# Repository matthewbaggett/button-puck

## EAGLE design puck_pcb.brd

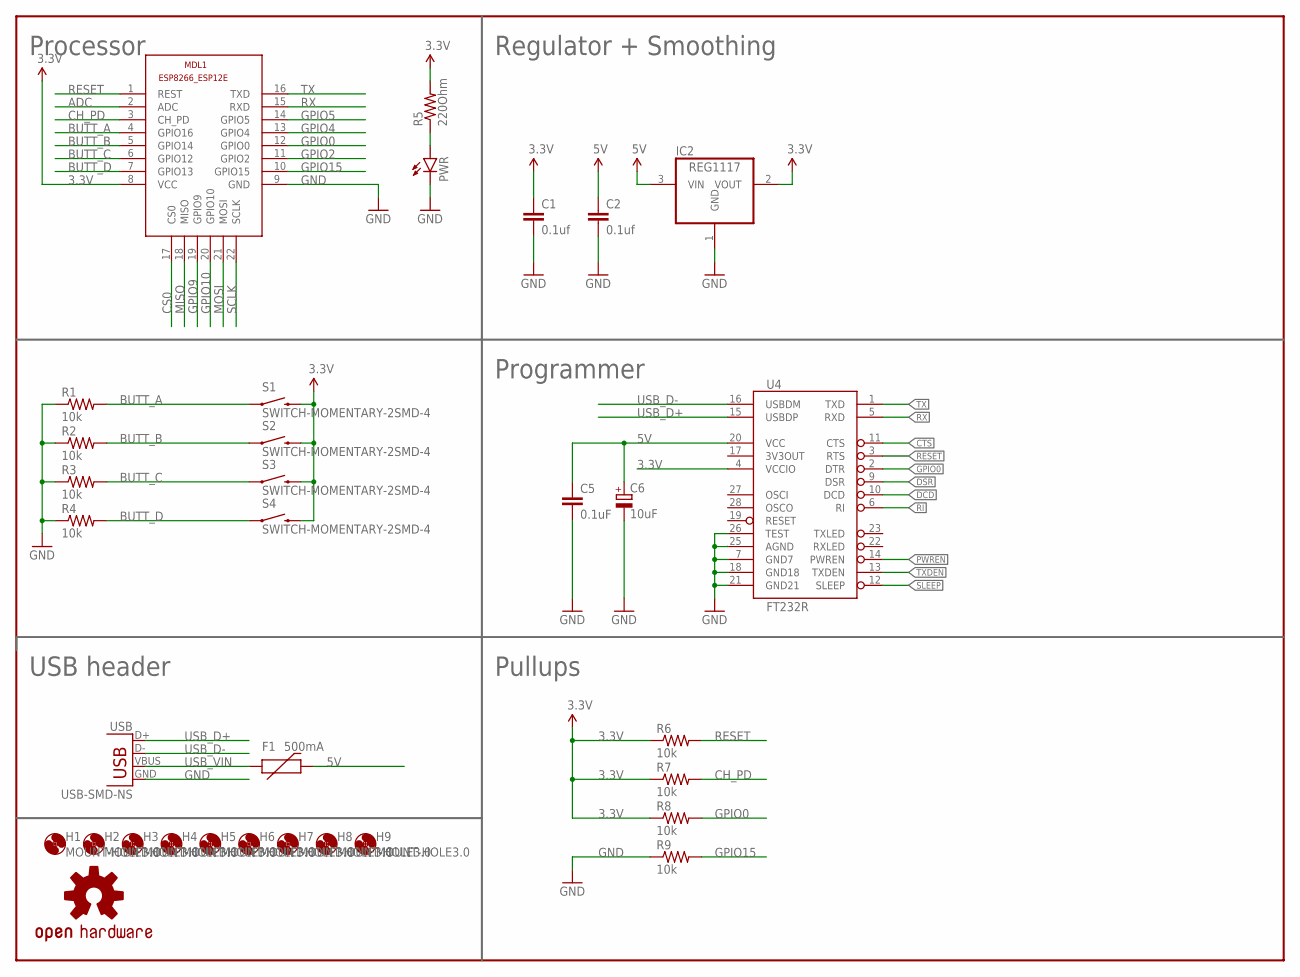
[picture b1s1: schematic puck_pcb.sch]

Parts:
C1, C2: 0.1uf; 1206
C5: 0.1uF; C1206K
C6: 10uF; SMC_A
F1: 500mA; PTC-1206
FRAME2: FRAME-LETTERNO_PACKAGE; DUMMY
H1, H2, H3, H4, H5, H6, H7, H8, H9: MOUNT-HOLE3.0; 3,0
IC2: REG1117; SOT223
LOGO1: OSHW-LOGOS; OSHW-LOGO-S
MDL1: ESP8266-12EESP8266-ESP12E; ESP8266-ESP12E
PWR: LED1206; LED-1206
R1, R2, R3, R4, R6, R7, R8, R9: 10k; 1206
R5: 220Ohm; 1206
S1, S2, S3, S4: SWITCH-MOMENTARY-2SMD-4; TACTILE_SWITCH_TALL
U4: FT232R; SSOP28DB
USB: USB-SMD-NS; USB-MINIB-NOSTOP

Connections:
3.3V: C1.1, IC2.2 (VOUT), MDL1.8 (VCC), R5.2, R6.1, R7.1, R8.1, S1.B2 (2), S2.B2 (2), S3.B2 (2), S4.B2 (2), U4.4 (VCCIO)
5V: C2.1, C5.1, C6.+, F1.2, IC2.3 (VIN), U4.20 (VCC)
ADC: MDL1.2 (ADC)
BUTT_A: MDL1.4 (GPIO16), R1.2, S1.A2 (1)
BUTT_B: MDL1.5 (GPIO14), R2.2, S2.A2 (1)
BUTT_C: MDL1.6 (GPIO12), R3.2, S3.A2 (1)
BUTT_D: MDL1.7 (GPIO13), R4.2, S4.A2 (1)
CH_PD: MDL1.3 (CH_PD), R7.2
CS0: MDL1.17 (CS0)
CTS: U4.11 (CTS)
DCD: U4.10 (DCD)
DSR: U4.9 (DSR)
GND: C1.2, C2.2, C5.2, C6.-, IC2.1 (GND), MDL1.9 (GND), PWR.C, R1.1, R2.1, R3.1, R4.1, R9.1, U4.7 (GND7), U4.18 (GND18), U4.21 (GND21), U4.25 (AGND), U4.26 (TEST), USB.GND
GPIO0: MDL1.12 (GPIO0), R8.2, U4.2 (DTR)
GPIO2: MDL1.11 (GPIO2)
GPIO4: MDL1.13 (GPIO4)
GPIO5: MDL1.14 (GPIO5)
GPIO9: MDL1.19 (GPIO9)
GPIO10: MDL1.20 (GPIO10)
GPIO15: MDL1.10 (GPIO15), R9.2
MISO: MDL1.18 (MISO)
MOSI: MDL1.21 (MOSI)
unnamed: PWR.A, R5.1
PWREN: U4.14 (PWREN)
RESET: MDL1.1 (REST), R6.2, U4.3 (RTS)
RI: U4.6 (RI)
RX: MDL1.15 (RXD), U4.5 (RXD)
SCLK: MDL1.22 (SCLK)
SLEEP: U4.12 (SLEEP)
TX: MDL1.16 (TXD), U4.1 (TXD)
TXDEN: U4.13 (TXDEN)
USB_D+: U4.15 (USBDP), USB.D+
USB_D-: U4.16 (USBDM), USB.D-
USB_VIN: F1.1, USB.VBUS

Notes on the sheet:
Programmer
Regulator + Smoothing
Processor
USB header
Pullups

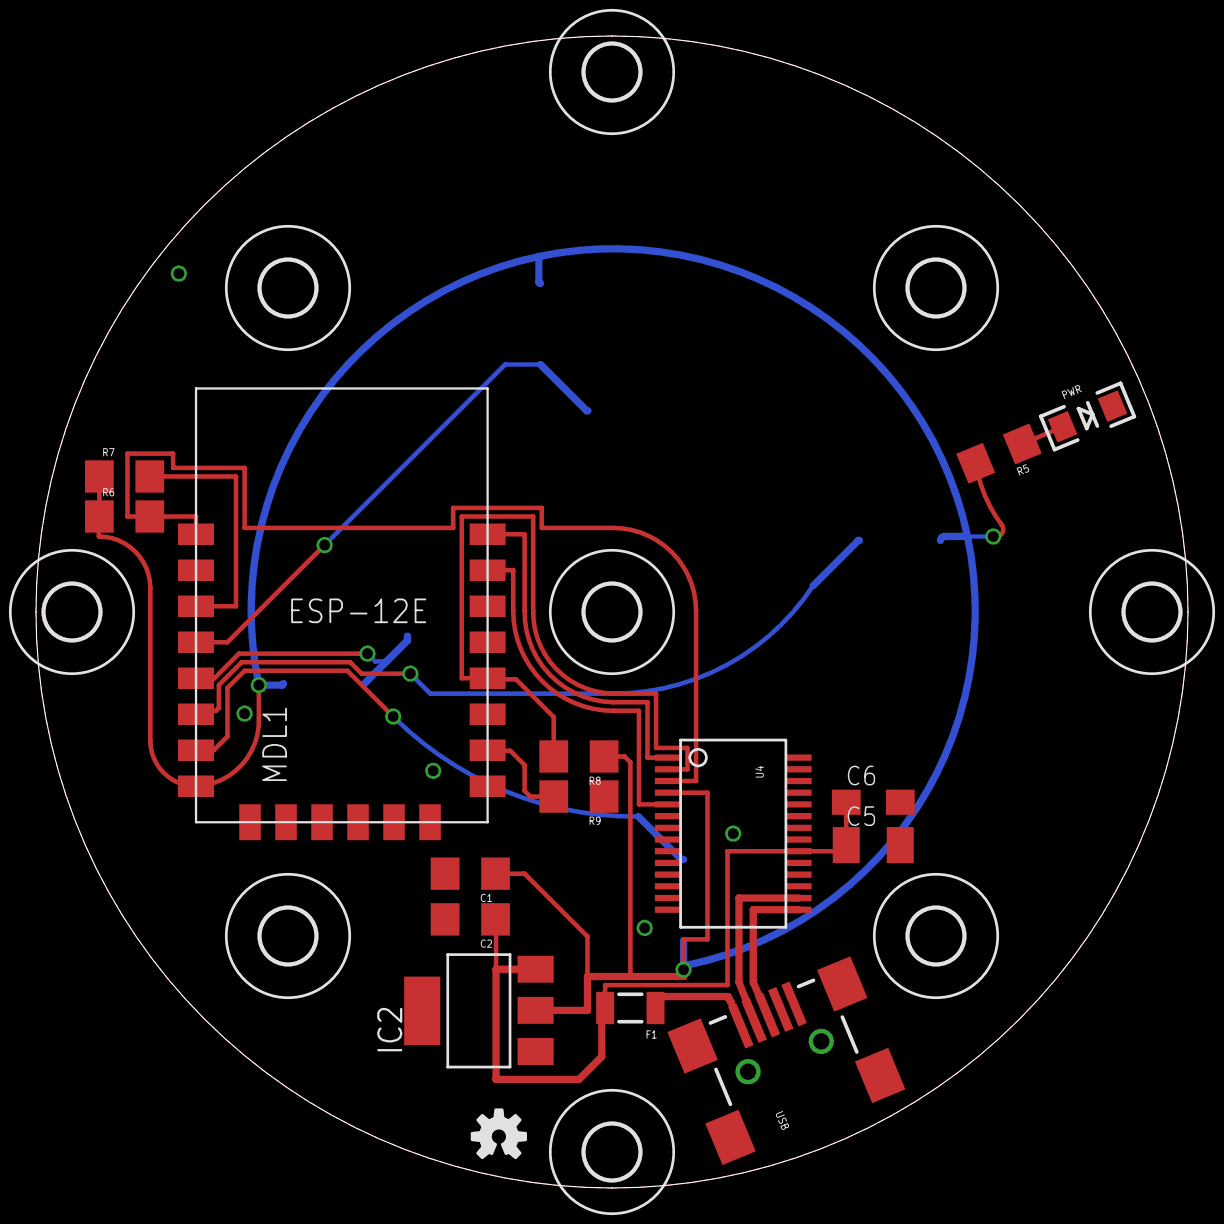
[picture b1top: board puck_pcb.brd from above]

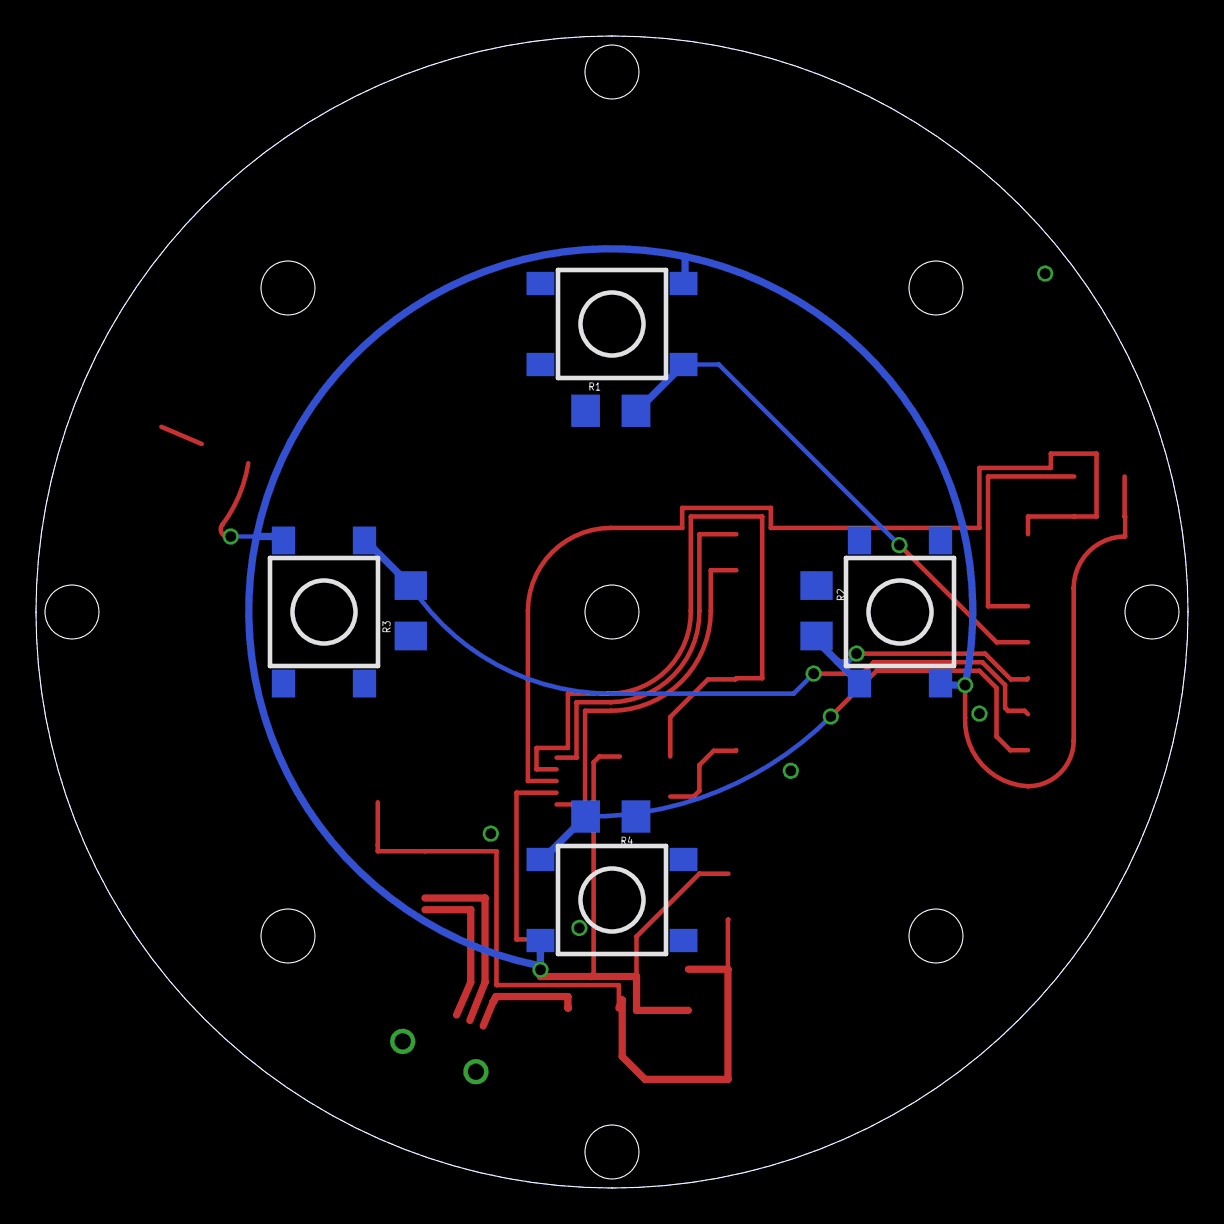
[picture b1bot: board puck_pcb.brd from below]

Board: 2 copper layers, 64.0 x 64.0 mm, 34 parts (8 on the bottom side), 17 nets.

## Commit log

2015-10-26 Initial board revision
2015-10-26 Initial model STLs
2015-10-26 Accidentally committed the wrong STL
2015-10-26 Make cover more printable
2015-10-26 Make the lettering deeper
2015-10-26 Make the cover slightly larger, increase the button bores

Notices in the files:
parts and their libraries:
SparkFun-Electromechanical: Licensing: Creative Commons ShareAlike 4.0 International - https://creativecommons.org/licenses/by-sa/4.0
SparkFun-Aesthetics: Released under the Creative Commons Attribution Share-Alike 4.0 License
SparkFun-Aesthetics: https://creativecommons.org/licenses/by-sa/4.0
